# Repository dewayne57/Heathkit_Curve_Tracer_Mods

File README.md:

# Heathkit_Curve_Tracer_Mods
Several key modifications to the Heathkit IT-x121 series semiconductor curve tracers (IT-1121 and IT-3121).  These 
semiconductor curve tracers essentially are the same with minor differences.  The schematic is virtually identical 
between the two. 

The schematic for the IT-1121  is included for reference. 

## Sweep Generator Modification
The sweep generator as designed used a 120Hz pulse derived from the secondary power supply to clock a 7490 decade 
counter.  The output from the counter was a 4-bit BCD value that was used to turn on or off 4 different current 
sources.  The result was a maximum of 9 discrete curves.  To set the number of curves desired to any value between 
0 and 9, the circuit picked some of the current off the energized sources and used that to determine when to reset
the counter.  This reset point was determined using a 7.5Mohm potentiometer.  Very high resistance values were used
in this circuit to reduce loading of the current generators.  

The 7.5MOhm potentiometer is no longer available and is not a standard size.  Getting a replacement would require
a custom part which would be very expensive.  Also, the use of a potentiometer to set the reset point makes setting 
the number of curves somewhat inaccurate and requires a bit of guesswork/fiddling with the setting. 

The 120Hz sweep clock works, but is relatively slow and can result in some flickering.  

This modification replaces the current sense/feedback solution with a digital one. This eliminates the current 
sense, the need for extremely high value resistors, and the potentiometer.  It replaces the potentiometer with 
a 10 position rotary switch which corresponds to the 0-9 desired curves.  The rotary switch provides discrete 
positive detents that provide for accurate setting of the desired number of curves.

The 74LS90 BCD count is applied to a 74LS42 BCD-to-decimal decoder that outputs 1 of 10 signals.  These are then 
routed to the rotary switch for selection.  The selected signal (1 of 10) is then inverted and used to reset 
the 74LS90 counter when that count has been reached.  Note that the reset signal is generated on the terminal
count, so the desired count is not actually included.  Therefore, the switch routes decoded outputs of 1-9 
as well as the 10th position tied high to an inverter.  The inverter output is used to generate the reset 
pulse. 

For example, in position 3 (2 curves), as soon as the BCD count reaches 3, the counter is reset.  This results 
in only 2 curves being displayed.  Likewise, if the switch is in position 10 (9 curves), the reset pulse is 
never generated, allowing the counter to overflow from 9 back to 0, resulting in 9 curves. 

To install this modification,
1. Remove the 7490 (IC6) from the board, leave the socket.  The updated daughter card will plug into this 
   socket. 
2. Remove the current feedback components (R46, R47, R48, R49, R51, and R52).
3. The 10 position rotary switch replaces R47 on the front panel.
4. Remove the reset circuit (R43, R44, R45, Q17, and Q18). 
5. Build the daughter card and use a 14-pin jumper from J1 to the IC6 socket on the main board. 

## Logic Supply Regulation 
The original circuit only provided a simple, low-current +5V supply that was not terribly well regulated because
there was only the single 7490 counter chip.  With the modification above, the demand for the +5V supply 
increases, and the existing circuit is no longer sufficient. 

This modification removes the voltage drop resistor and replaces it with a LM7805 linear regulator.  The +15V 
side of the resistor is tied to the input of the LM7805.  The output of the LM7805 replaces the +5V side of 
the dropping resistor (the resistor is removed).  The ground leg of the LM7805 is tied to an available ground 
connection on the circuit. 

To install this modification,
1. Remove the dropping resistor R37. 
2. Wire the input pin of an LM7805 to the +15.5V side of R37.  This is best done by placing the LM7805 
   off-board and using wires to connect it to the board.  I recommend mounting the LM7805 to the aluminum 
   chassis somewhere (insulated) for heat dissipation. 
3. Wire the output of the LM7805 to the +5 side of R37.  Note, leave capacitor C7 in circuit. 
4. Wire the ground lead of the LM7805 to the ground side of C7.

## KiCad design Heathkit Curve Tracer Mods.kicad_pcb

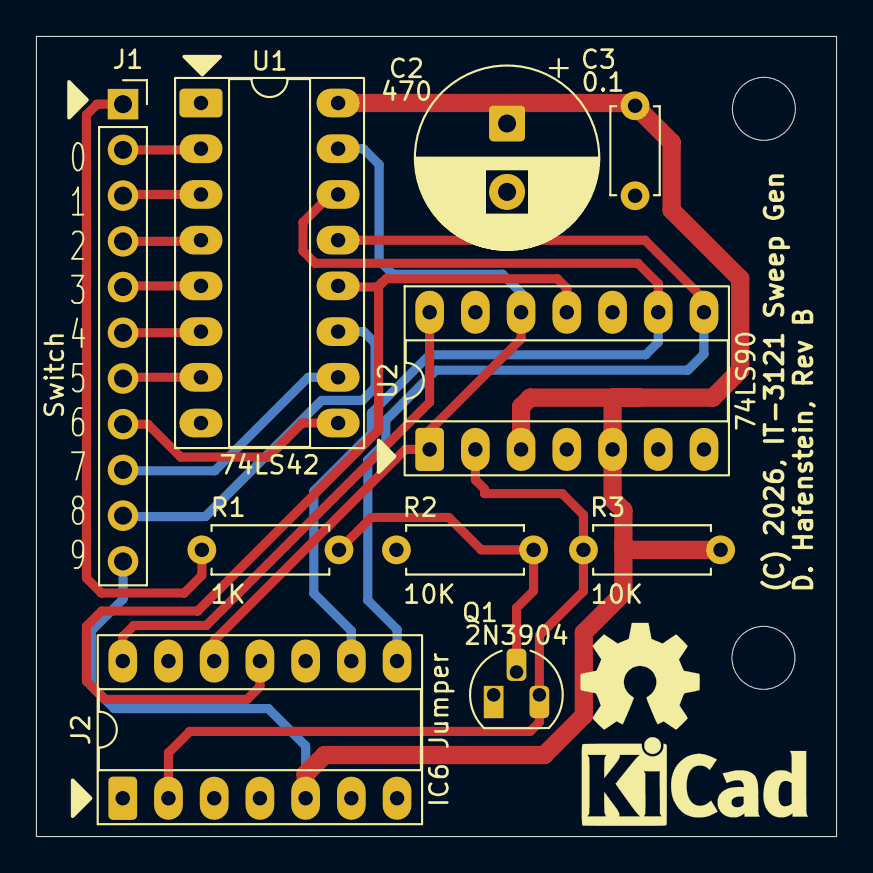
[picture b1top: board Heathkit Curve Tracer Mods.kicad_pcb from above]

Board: 2 copper layers, 44.5 x 44.5 mm, 10 parts (0 on the bottom side), 19 nets.

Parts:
C2: 470; CP_Radial_D10.0mm_P3.80mm
C3: 0.1; C_Disc_D4.7mm_W2.5mm_P5.00mm
J1: Switch; PinSocket_1x11_P2.54mm_Vertical
J2: IC6 Jumper; DIP-14_W7.62mm_Socket_LongPads
Q1: 2N3904; TO-92L_HandSolder
R1: 1K; R_Axial_DIN0207_L6.3mm_D2.5mm_P7.62mm_Horizontal
R2, R3: 10K; R_Axial_DIN0207_L6.3mm_D2.5mm_P7.62mm_Horizontal
U1: 74LS42; DIP-16_W7.62mm_Socket_LongPads
U2: 74LS90; DIP-14_W7.62mm_Socket_LongPads

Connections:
+5V: C2.1, C3.1, J1.11, J2.5, R3.1, U1.16 (VCC), U2.3 (R0(2)), U2.5 (VCC)
GND: C2.2, C3.2, J2.6, J2.10, Q1.1 (E), R2.2, U1.8 (GND), U2.6 (R9(1)), U2.7 (R9(2)), U2.10 (GND)
unnamed: J1.1, R1.1
unnamed: J1.2, U1.2 (1)
unnamed: J1.3, U1.3 (2)
unnamed: J1.4, U1.4 (3)
unnamed: J1.5, U1.5 (4)
unnamed: J1.6, U1.6 (5)
unnamed: J1.7, U1.7 (6)
unnamed: J1.8, U1.9 (7)
unnamed: J1.9, U1.10 (8)
unnamed: J1.10, U1.11 (9)
unnamed: J2.2, Q1.3 (C), R3.2, U2.2 (R0(1))
unnamed: J2.8, U1.13 (A2), U2.8 (Q2)
unnamed: J2.9, U1.14 (A1), U2.9 (Q1)
unnamed: J2.11, U1.12 (A3), U2.11 (Q3)
unnamed: J2.12, U1.15 (A0), U2.1 (CP1..3), U2.12 (Q0)
unnamed: J2.14, U2.14 (CP0)
unnamed: Q1.2 (B), R1.2, R2.1

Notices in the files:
Heathkit Curve Tracer Mods.kicad_pcb:
(C) 2026, IT-3121 Sweep Gen
